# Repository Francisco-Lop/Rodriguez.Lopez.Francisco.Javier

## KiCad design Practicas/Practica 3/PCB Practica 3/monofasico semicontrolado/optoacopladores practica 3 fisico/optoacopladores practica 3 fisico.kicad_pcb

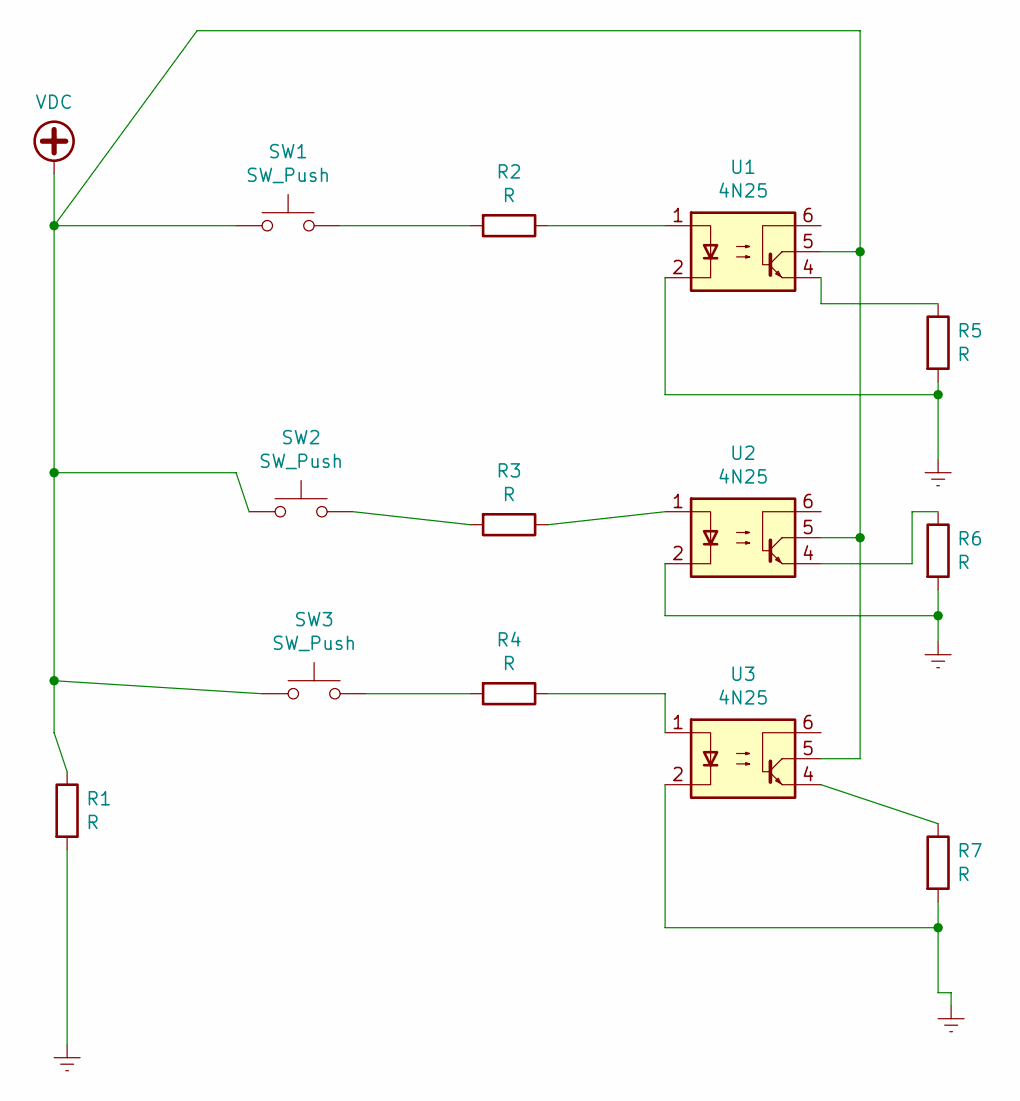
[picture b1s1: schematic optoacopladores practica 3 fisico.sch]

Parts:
R1, R2, R3, R4, R5, R6, R7: R; R_Axial_DIN0204_L3.6mm_D1.6mm_P5.08mm_Horizontal
SW1, SW2, SW3: SW_Push; R_Axial_DIN0204_L3.6mm_D1.6mm_P5.08mm_Horizontal
U1, U2, U3: 4N25; DIP-6_W7.62mm

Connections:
Earth: R1.2, R5.2, R6.2, R7.2, U1.2, U2.2, U3.2
unnamed: R2.1, U1.1
unnamed: R2.2, SW1.2
unnamed: R3.1, U2.1
unnamed: R3.2, SW2.2
unnamed: R4.1, U3.1
unnamed: R4.2, SW3.2
unnamed: R5.1, U1.4
unnamed: R6.1, U2.4
unnamed: R7.1, U3.4
VDC: R1.1, SW1.1, SW2.1, SW3.1, U1.5, U2.5, U3.5

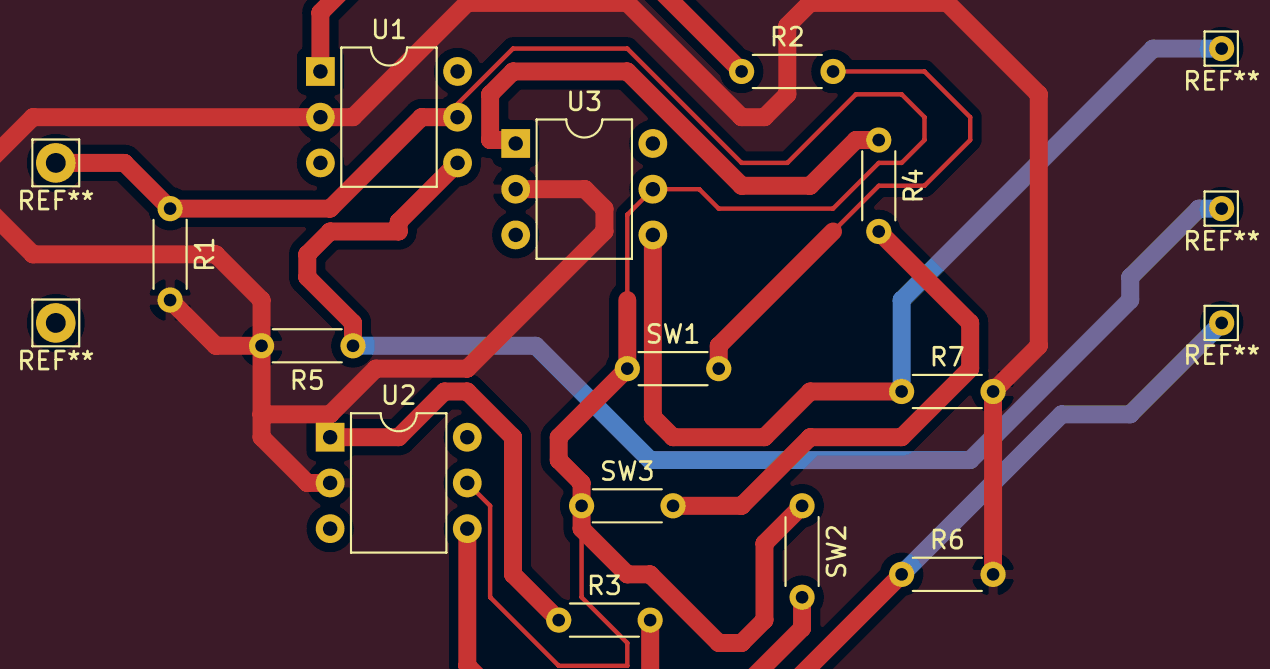
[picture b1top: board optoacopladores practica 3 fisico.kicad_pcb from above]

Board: 2 copper layers, 13 parts (0 on the bottom side), 11 nets.

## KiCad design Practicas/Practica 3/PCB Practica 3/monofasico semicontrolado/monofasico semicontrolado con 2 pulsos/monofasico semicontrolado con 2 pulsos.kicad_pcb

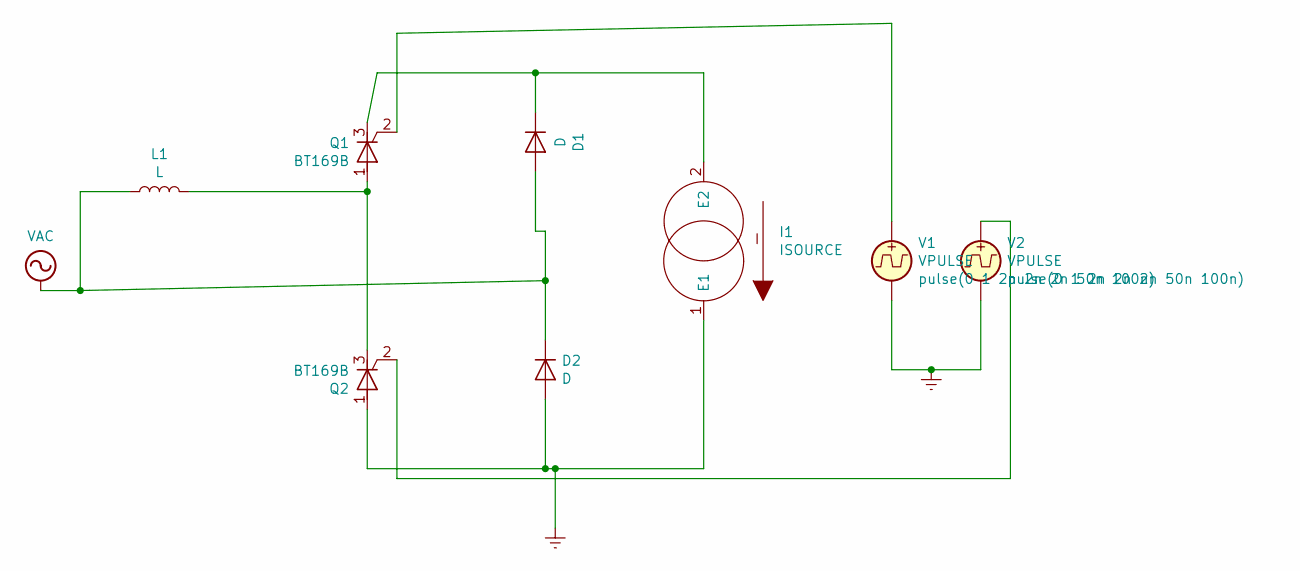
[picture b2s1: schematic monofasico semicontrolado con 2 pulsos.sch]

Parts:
D1, D2: D; D_5KP_P10.16mm_Horizontal
I1: ISOURCE; R_Axial_DIN0204_L3.6mm_D1.6mm_P2.54mm_Vertical
L1: L; Choke_Schaffner_RN114-04-22.5x21.5mm
Q1, Q2: BT169B; TO-92_Inline
V1, V2: VPULSE; R_Axial_DIN0204_L3.6mm_D1.6mm_P2.54mm_Vertical

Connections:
Earth: D2.2 (A), I1.1 (E1), Q2.1 (A), V1.2, V2.2
unnamed: D1.1 (K), I1.2 (E2), Q1.3 (K)
unnamed: L1.2, Q1.1 (A), Q2.3 (K)
unnamed: Q1.2 (G), V1.1
unnamed: Q2.2 (G), V2.1
VAC: D1.2 (A), D2.1 (K), L1.1

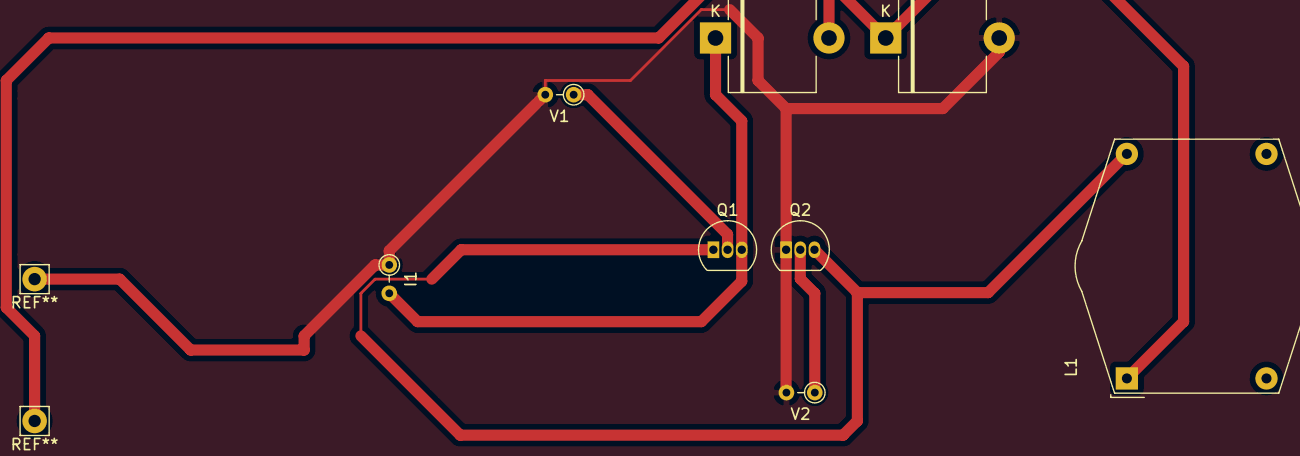
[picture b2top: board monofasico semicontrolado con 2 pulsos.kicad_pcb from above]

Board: 2 copper layers, 8 parts (0 on the bottom side), 6 nets.

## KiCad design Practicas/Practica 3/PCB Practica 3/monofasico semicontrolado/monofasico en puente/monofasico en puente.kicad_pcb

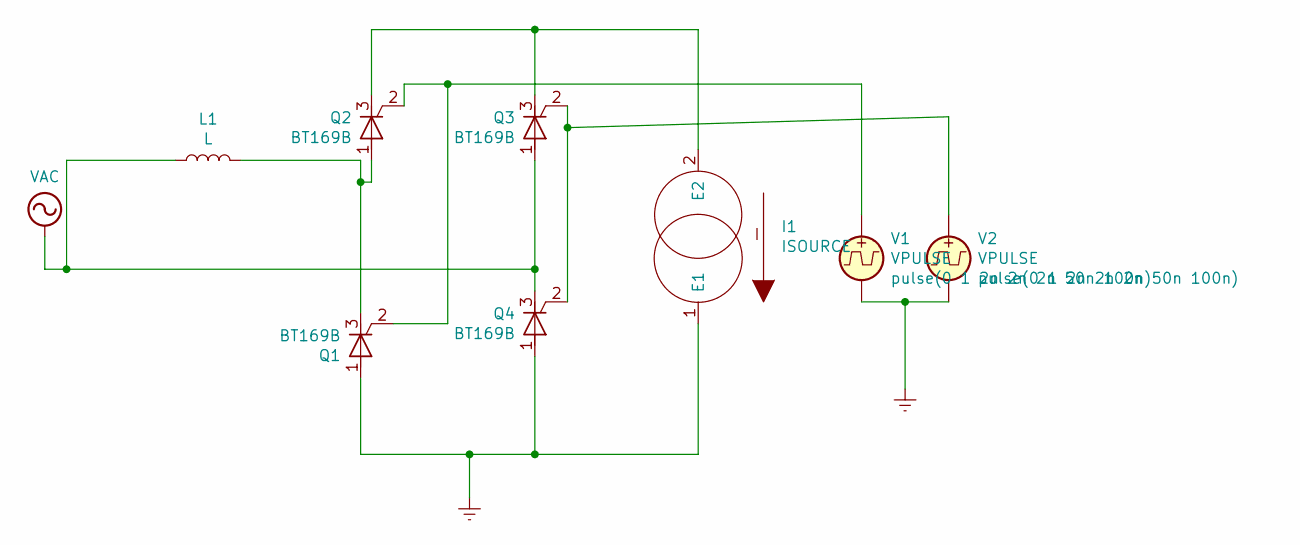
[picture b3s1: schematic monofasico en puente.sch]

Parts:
I1: ISOURCE; L_Axial_L5.3mm_D2.2mm_P7.62mm_Horizontal_Vishay_IM-1
L1: L; L_Axial_L5.3mm_D2.2mm_P7.62mm_Horizontal_Vishay_IM-1
Q1, Q2, Q3, Q4: BT169B; TO-92_Inline
V1, V2: VPULSE; PinHeader_1x02_P1.00mm_Vertical_SMD_Pin1Left

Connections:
Earth: I1.1 (E1), Q1.1 (A), Q4.1 (A), V1.2, V2.2
unnamed: I1.2 (E2), Q2.3 (K), Q3.3 (K)
unnamed: L1.2, Q1.3 (K), Q2.1 (A)
unnamed: Q1.2 (G), Q2.2 (G), V1.1
unnamed: Q3.2 (G), Q4.2 (G), V2.1
VAC: L1.1, Q3.1 (A), Q4.3 (K)

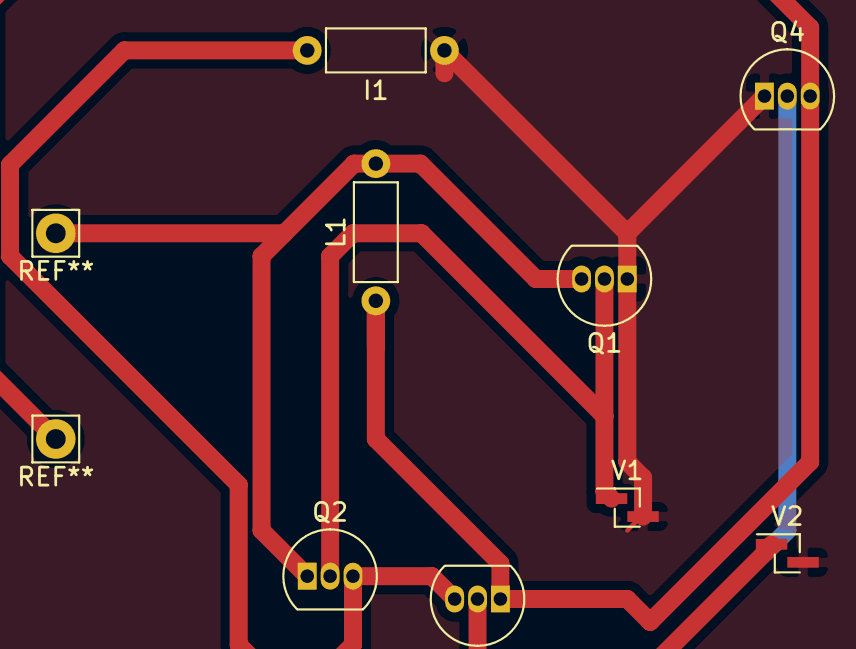
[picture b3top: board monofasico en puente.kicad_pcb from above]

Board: 2 copper layers, 8 parts (0 on the bottom side), 6 nets.

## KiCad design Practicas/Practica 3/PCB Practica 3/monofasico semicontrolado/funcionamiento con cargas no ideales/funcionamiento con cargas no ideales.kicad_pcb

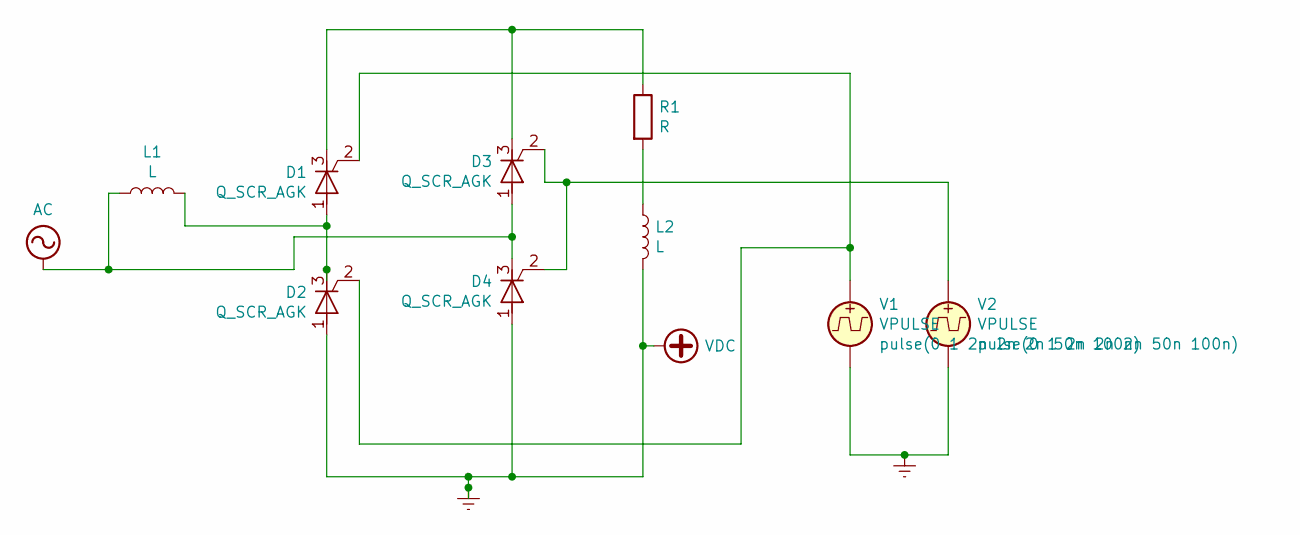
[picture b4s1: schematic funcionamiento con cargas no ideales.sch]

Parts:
D1, D2, D3, D4: Q_SCR_AGK; Potentiometer_ACP_CA9-H2,5_Horizontal
L1, L2: L; L_Axial_L5.3mm_D2.2mm_P7.62mm_Horizontal_Vishay_IM-1
R1: R; R_Axial_DIN0204_L3.6mm_D1.6mm_P7.62mm_Horizontal
V1, V2: VPULSE; R_Axial_DIN0207_L6.3mm_D2.5mm_P10.16mm_Horizontal

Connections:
AC: D3.1 (A), D4.3 (K), L1.1
Earth: D2.1 (A), D4.1 (A), L2.2, V1.2, V2.2
unnamed: D1.1 (A), D2.3 (K), L1.2
unnamed: D1.2 (G), D2.2 (G), V1.1
unnamed: D1.3 (K), D3.3 (K), R1.1
unnamed: D3.2 (G), D4.2 (G), V2.1
unnamed: L2.1, R1.2

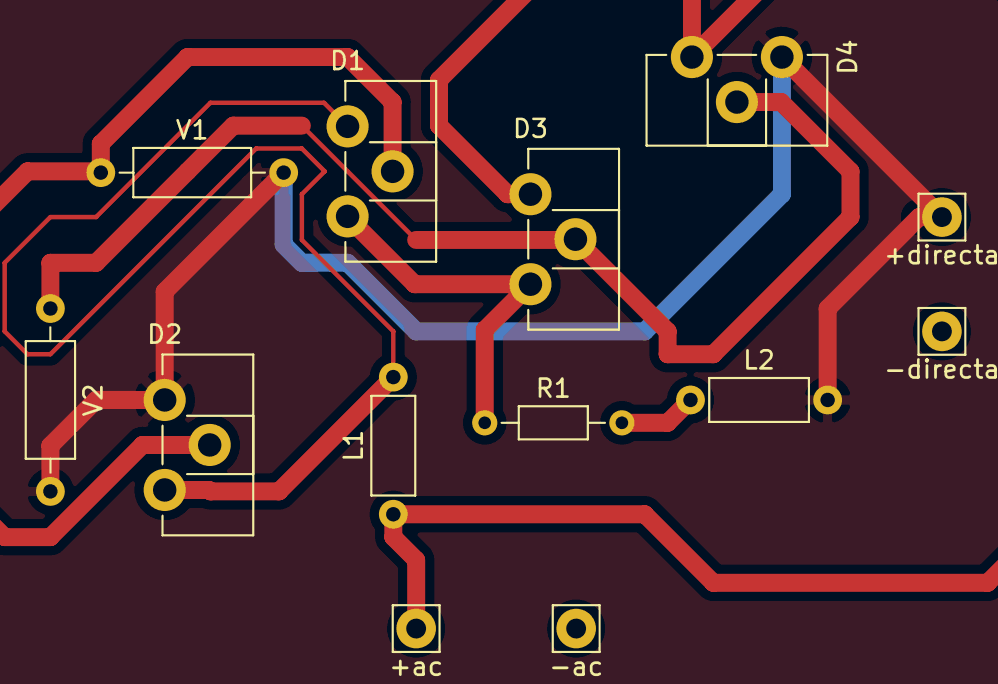
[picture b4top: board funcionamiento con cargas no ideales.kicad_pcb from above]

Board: 2 copper layers, 13 parts (0 on the bottom side), 7 nets.

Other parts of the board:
+ac: Pin_D1.1mm_L8.5mm_W2.5mm_FlatFork
+directa: Pin_D1.1mm_L8.5mm_W2.5mm_FlatFork
-ac: Pin_D1.1mm_L8.5mm_W2.5mm_FlatFork
-directa: Pin_D1.1mm_L8.5mm_W2.5mm_FlatFork

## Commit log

2019-09-18 mi commit
2019-11-10 Create Ev_1_1_Circuitos_de_rectiicacion_no_controlados
